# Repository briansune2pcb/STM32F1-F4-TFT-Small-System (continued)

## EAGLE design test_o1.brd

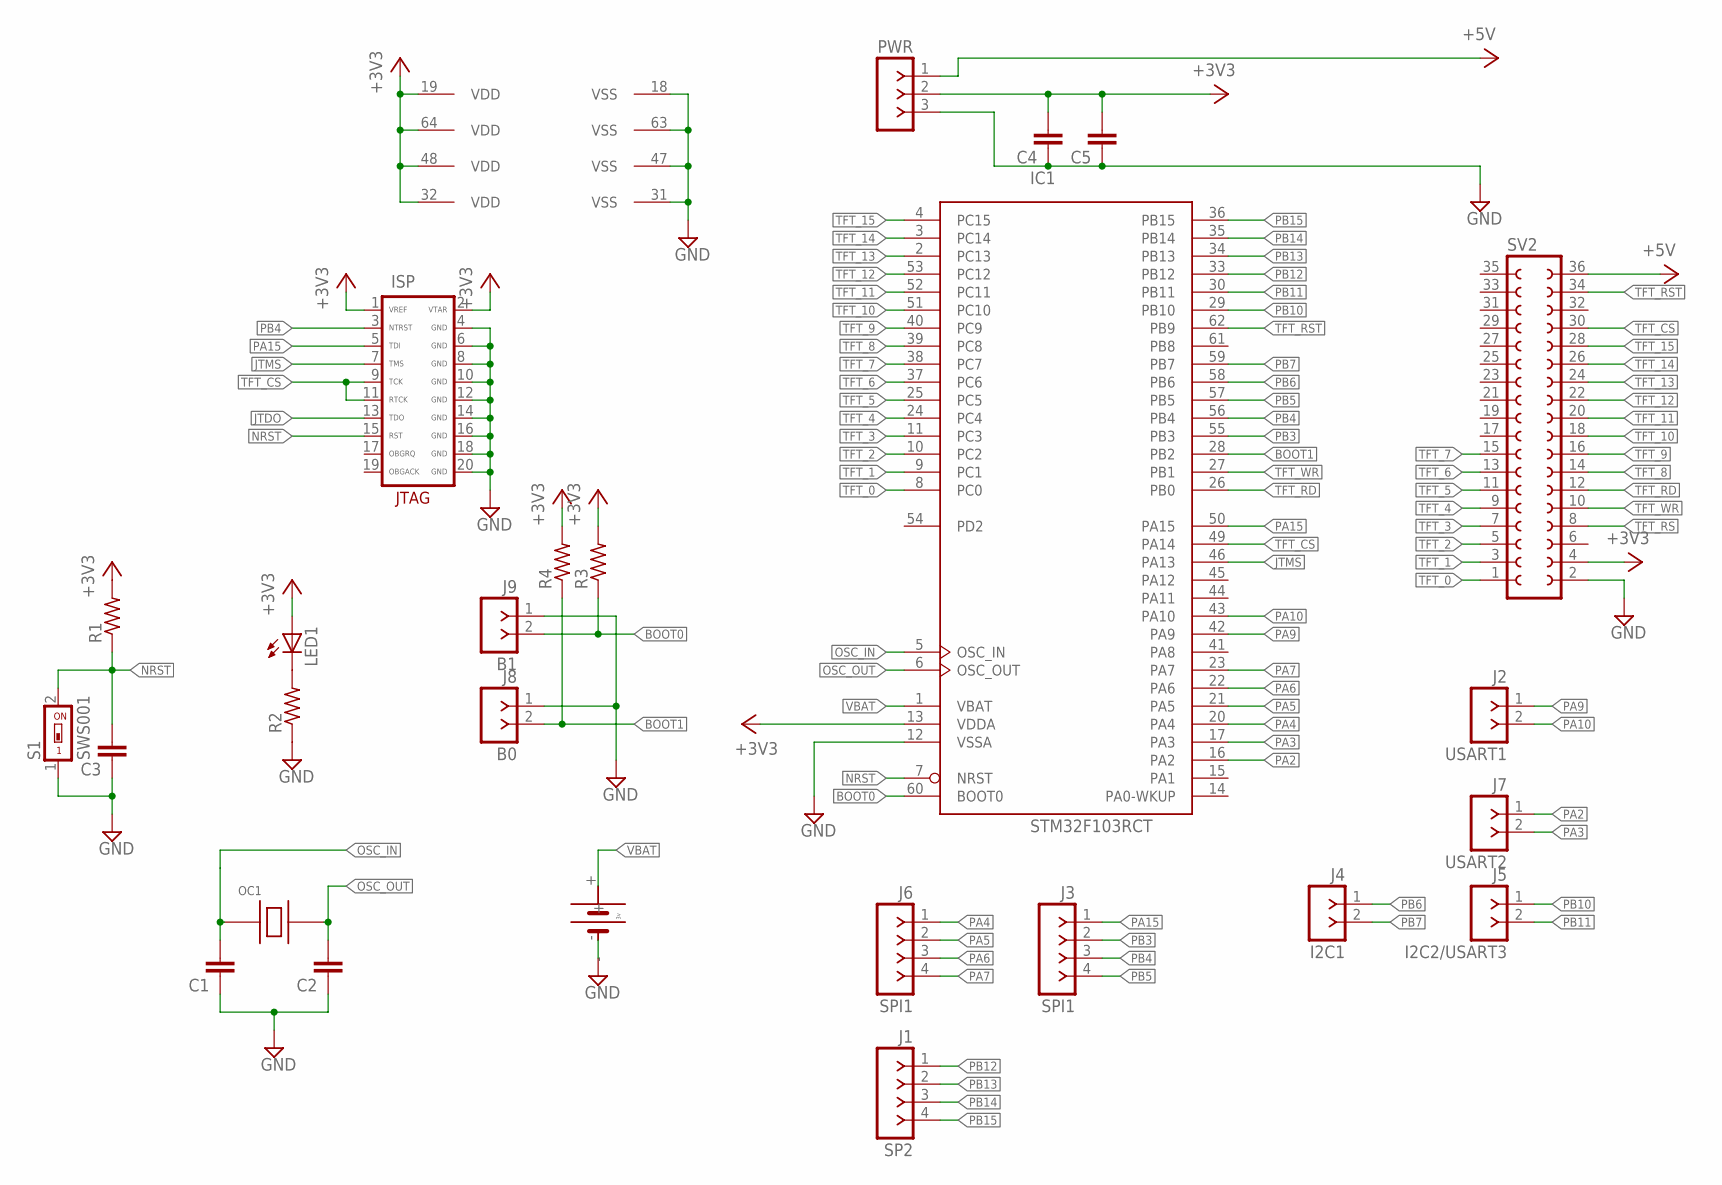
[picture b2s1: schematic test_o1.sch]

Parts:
C1, C2, C3, C4, C5: C-EUC1206; C1206
IC1: STM32F103RCT; LQFP64
ISP: JTAG; PAK100/2500-20
J1: SP2; SIP-100-04-40
J2: USART1; SIP-100-02-40
J3, J6: SPI1; SIP-100-04-40
J4: I2C1; SIP-100-02-40
J5: I2C2/USART3; SIP-100-02-40
J7: USART2; SIP-100-02-40
J8: B0; SIP-100-02-40
J9: B1; SIP-100-02-40
LED1: LEDSML1206; SML1206
OC1: SMAQ-7050B; IQG7050B
PWR: F-1X03-SIP-100-40; SIP-100-03-40
R1, R2, R3, R4: R-US_R1206; R1206
S1: SWS001; SMS-001
SV2: FE18-2
U$2: 1220BATTERY_SF; 1220BATTERY

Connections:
+3V3: C4.2, C5.2, IC1.13 (VDDA), IC1.19 (VDD), IC1.32 (VDD), IC1.48 (VDD), IC1.64 (VDD), ISP.1 (VREF), ISP.2 (VTAR), LED1.A, PWR.2, R1.2, R3.2, R4.2, SV2.4
+5V: PWR.1, SV2.36
BOOT0: IC1.60 (BOOT0), J9.2, R3.1
BOOT1: IC1.28 (PB2), J8.2, R4.1
GND: C1.1, C2.1, C3.1, C4.1, C5.1, IC1.12 (VSSA), IC1.18 (VSS), IC1.31 (VSS), IC1.47 (VSS), IC1.63 (VSS), ISP.4 (GND), ISP.6 (GND), ISP.8 (GND), ISP.10 (GND), ISP.12 (GND), ISP.14 (GND), ISP.16 (GND), ISP.18 (GND), ISP.20 (GND), J8.1, J9.1, PWR.3, R2.1, S1.1, SV2.2, U$2.-
JTDO: ISP.13 (TDO)
JTMS: IC1.46 (PA13), ISP.7 (TMS)
unnamed: LED1.C, R2.2
NRST: C3.2, IC1.7 (NRST), ISP.15 (RST), R1.1, S1.2
OSC_IN: C1.2, IC1.5 (OSC_IN), OC1.P$1 (PIN1)
OSC_OUT: C2.2, IC1.6 (OSC_OUT), OC1.P$3 (PIN2)
PA2: IC1.16 (PA2), J7.1
PA3: IC1.17 (PA3), J7.2
PA4: IC1.20 (PA4), J6.1
PA5: IC1.21 (PA5), J6.2
PA6: IC1.22 (PA6), J6.3
PA7: IC1.23 (PA7), J6.4
PA9: IC1.42 (PA9), J2.1
PA10: IC1.43 (PA10), J2.2
PA15: IC1.50 (PA15), ISP.5 (TDI), J3.1
PB3: IC1.55 (PB3), J3.2
PB4: IC1.56 (PB4), ISP.3 (NTRST), J3.3
PB5: IC1.57 (PB5), J3.4
PB6: IC1.58 (PB6), J4.1
PB7: IC1.59 (PB7), J4.2
PB10: IC1.29 (PB10), J5.1
PB11: IC1.30 (PB11), J5.2
PB12: IC1.33 (PB12), J1.1
PB13: IC1.34 (PB13), J1.2
PB14: IC1.35 (PB14), J1.3
PB15: IC1.36 (PB15), J1.4
TFT_0: IC1.8 (PC0), SV2.1
TFT_1: IC1.9 (PC1), SV2.3
TFT_2: IC1.10 (PC2), SV2.5
TFT_3: IC1.11 (PC3), SV2.7
TFT_4: IC1.24 (PC4), SV2.9
TFT_5: IC1.25 (PC5), SV2.11
TFT_6: IC1.37 (PC6), SV2.13
TFT_7: IC1.38 (PC7), SV2.15
TFT_8: IC1.39 (PC8), SV2.14
TFT_9: IC1.40 (PC9), SV2.16
TFT_10: IC1.51 (PC10), SV2.18
TFT_11: IC1.52 (PC11), SV2.20
TFT_12: IC1.53 (PC12), SV2.22
TFT_13: IC1.2 (PC13), SV2.24
TFT_14: IC1.3 (PC14), SV2.26
TFT_15: IC1.4 (PC15), SV2.28
TFT_CS: IC1.49 (PA14), ISP.9 (TCK), ISP.11 (RTCK), SV2.30
TFT_RD: IC1.26 (PB0), SV2.12
TFT_RS: SV2.8
TFT_RST: IC1.62 (PB9), SV2.34
TFT_WR: IC1.27 (PB1), SV2.10
VBAT: IC1.1 (VBAT), U$2.+

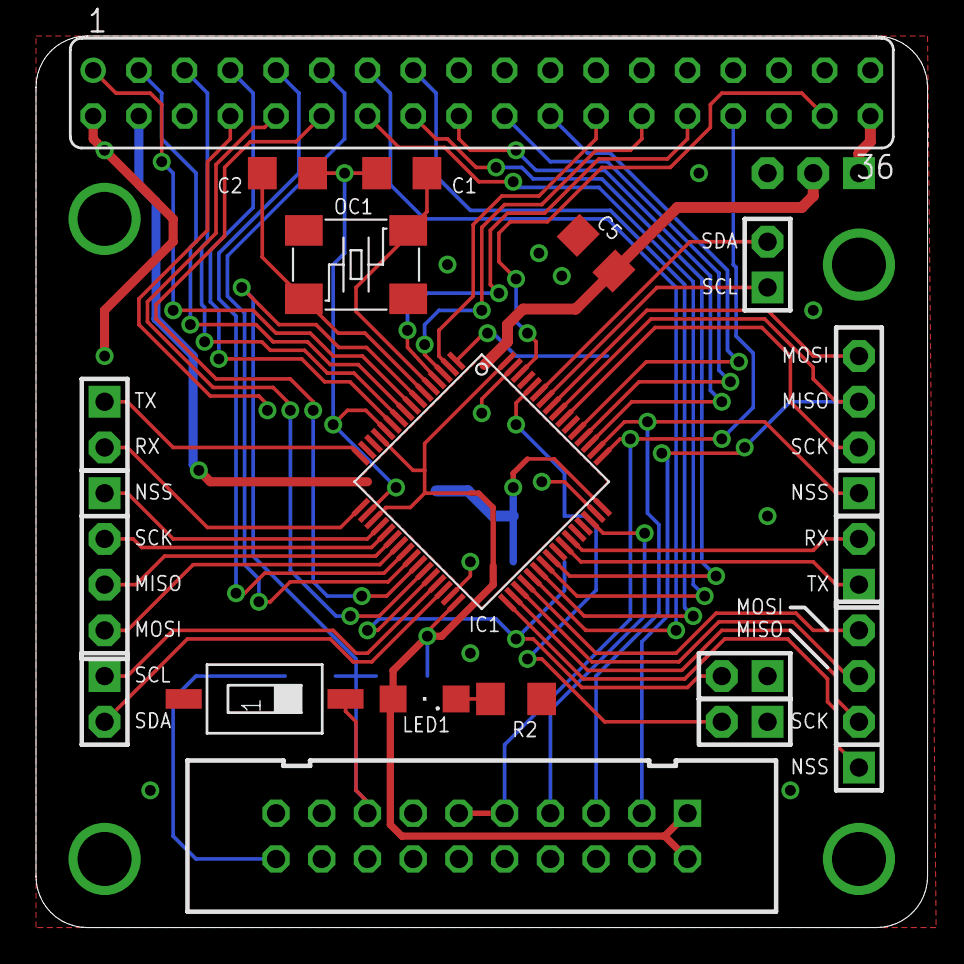
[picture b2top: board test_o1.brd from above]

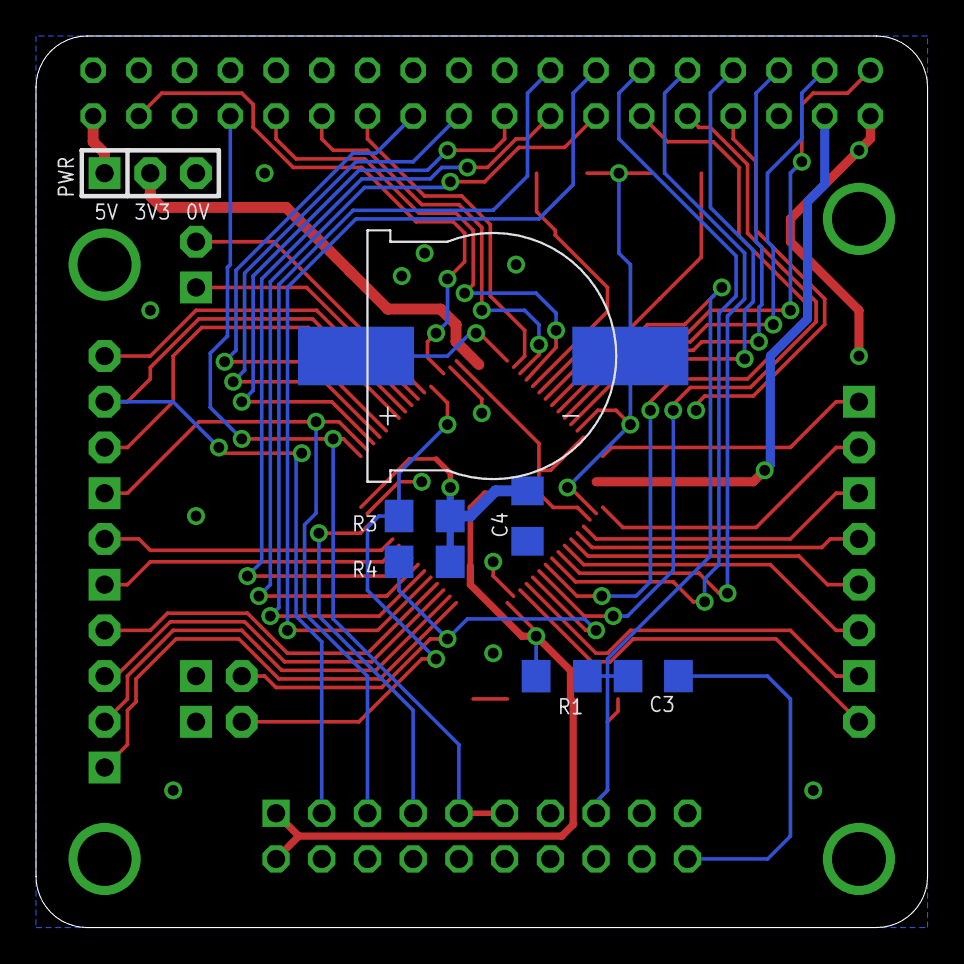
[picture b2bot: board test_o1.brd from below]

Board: 2 copper layers, 49.5 x 49.5 mm, 26 parts (7 on the bottom side), 51 nets.

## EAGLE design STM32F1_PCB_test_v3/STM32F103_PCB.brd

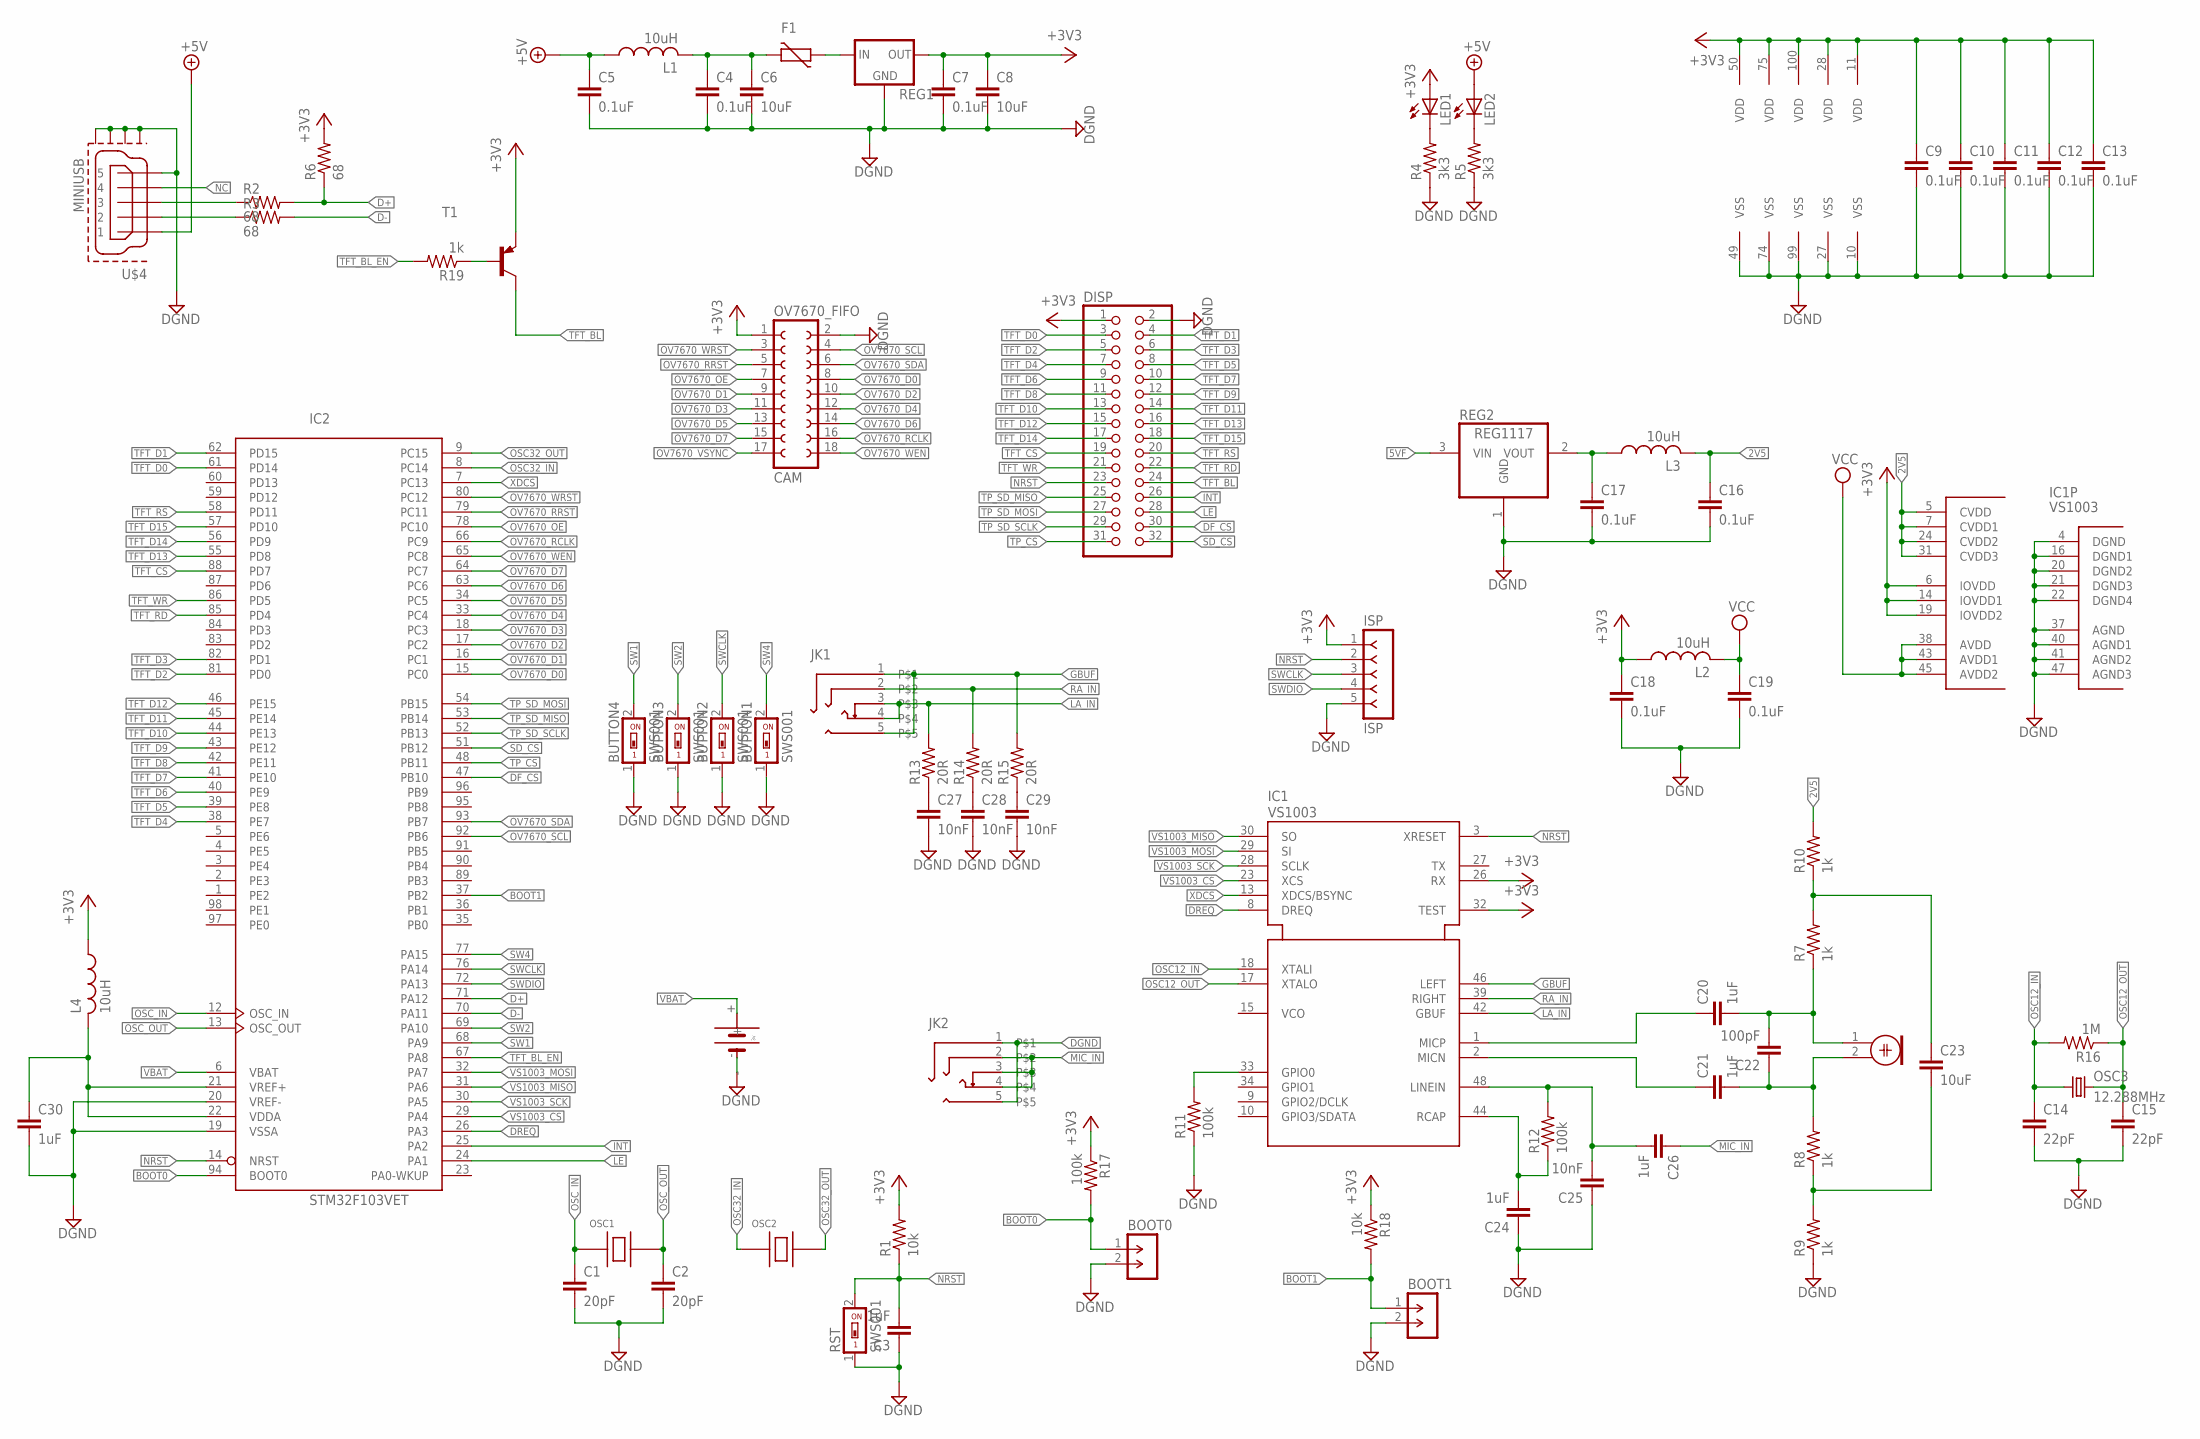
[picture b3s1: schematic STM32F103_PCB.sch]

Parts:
BOOT0, BOOT1: M-1X02-SIP-100-32; SIP-100-02-32
BUTTON1, BUTTON2, BUTTON3, BUTTON4: SWS001; SMS-001
C1, C2: 20pF; C1206
C3, C20, C21, C24, C26, C30: 1uF; C1206
C4, C5, C7, C9, C10, C11, C12, C13, C16, C17, C18, C19: 0.1uF; C1206
C6, C8, C23: 10uF; C1206
C14, C15: 22pF; C1206
C22: 100pF; C1206
C25, C27, C28, C29: 10nF; C1206
CAM: OV7670_FIFO; FE09-2
DISP: PINHD-2X16; 2X16
F1: VARISTORCN1206; CT/CN1206
IC1: VS1003; LQFP48
IC2: STM32F103VET; LQFP100
ISP: ISP; SIP-100-05-40
JK1, JK2: HEADPHONE_XXX1
L1, L2, L3, L4: 10uH; L3216C
LED1, LED2: LEDSML1206; SML1206
MIC: ELECTRET_MICROPHON-WM-61A; WM-61A
OSC1: 8.0MHz; IQG7050B
OSC2: 32.768kHz; IQG5032A
OSC3: 12.288MHz; HC49UP
R1, R18: 10k; R1206
R2, R3, R6: 68; R1206
R4, R5: 3k3; R1206
R7, R8, R9, R10, R19: 1k; R1206
R11, R12, R17: 100k; R1206
R13, R14, R15: 20R; R1206
R16: 1M; R1206
REG1: XC63FPM; SOT23
REG2: REG1117; SOT223
RST: SWS001; SMS-001
T1: MMBT3906LT1-PNP-SOT23-BEC; SOT23-BEC
U$1: 1220BATTERY_SF; 1220BATTERY
U$4: MINIUSB; MK5P

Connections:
2V5: C16.1, IC1.5 (CVDD), IC1.7 (CVDD1), IC1.24 (CVDD2), IC1.31 (CVDD3), L3.2, R10.2
5VF: F1.1, REG1.3 (IN), REG2.3 (VIN)
+3V3: C7.1, C8.1, C9.1, C10.1, C11.1, C12.1, C13.1, C18.1, CAM.1, DISP.1, IC1.6 (IOVDD), IC1.14 (IOVDD1), IC1.19 (IOVDD2), IC1.26 (RX), IC1.32 (TEST), IC2.11 (VDD), IC2.28 (VDD), IC2.50 (VDD), IC2.75 (VDD), IC2.100 (VDD), ISP.1, L2.1, L4.1, LED1.A, R1.2, R6.2, R17.1, R18.1, REG1.2 (OUT), T1.E
+5V: C5.1, L1.1, LED2.A, U$4.1
BOOT0: BOOT0.1, IC2.94 (BOOT0), R17.2
BOOT1: BOOT1.1, IC2.37 (PB2), R18.2
D+: IC2.71 (PA12), R2.2, R6.1
D-: IC2.70 (PA11), R3.2
DF_CS: DISP.30, IC2.47 (PB10)
DGND: BOOT0.2, BOOT1.2, BUTTON1.1, BUTTON2.1, BUTTON3.1, BUTTON4.1, C1.2, C2.2, C3.1, C4.2, C5.2, C6.2, C7.2, C8.2, C9.2, C10.2, C11.2, C12.2, C13.2, C14.2, C15.2, C16.2, C17.2, C18.2, C19.2, C24.1, C25.1, C27.2, C28.2, C29.2, C30.2, CAM.2, DISP.2, IC1.4 (DGND), IC1.16 (DGND1), IC1.20 (DGND2), IC1.21 (DGND3), IC1.22 (DGND4), IC1.37 (AGND), IC1.40 (AGND1), IC1.41 (AGND2), IC1.47 (AGND3), IC2.10 (VSS), IC2.19 (VSSA), IC2.20 (VREF-), IC2.27 (VSS), IC2.49 (VSS), IC2.74 (VSS), IC2.99 (VSS), ISP.5, JK2.1, JK2.5, R4.1, R5.1, R9.1, R11.1, REG1.1 (GND), REG2.1 (GND), RST.1, U$1.-, U$4.5, U$4.P$1 (GND1), U$4.P$2 (GND2), U$4.P$6 (GND3), U$4.P$7 (GND4)
DREQ: IC1.8 (DREQ), IC2.26 (PA3)
GBUF: IC1.46 (LEFT), JK1.1, JK1.5, R15.2
INT: DISP.26, IC2.25 (PA2)
LA_IN: IC1.42 (GBUF), JK1.3, JK1.4, R13.2
LE: DISP.28, IC2.24 (PA1)
MIC_IN: C26.1, JK2.2, JK2.3, JK2.4
unnamed: C17.1, L3.1, REG2.2 (VOUT)
unnamed: R3.1, U$4.2
unnamed: R2.1, U$4.3
unnamed: C4.1, C6.1, F1.2, L1.2
unnamed: LED1.C, R4.2
unnamed: LED2.C, R5.2
unnamed: C20.1, IC1.1 (MICP)
unnamed: C21.1, IC1.2 (MICN)
unnamed: C21.2, C22.1, MIC.2, R8.2
unnamed: C20.2, C22.2, MIC.1, R7.1
unnamed: C23.1, R7.2, R10.1
unnamed: C23.2, R8.1, R9.2
unnamed: IC1.33 (GPIO0), R11.2
unnamed: C24.2, IC1.44 (RCAP), R12.1
unnamed: C25.2, C26.2, IC1.48 (LINEIN), R12.2
unnamed: C27.1, R13.1
unnamed: R19.1, T1.B
unnamed: C28.1, R14.1
unnamed: C29.1, R15.1
unnamed: C30.1, IC2.21 (VREF+), IC2.22 (VDDA), L4.2
NC: U$4.4
NRST: C3.2, DISP.23, IC1.3 (XRESET), IC2.14 (NRST), ISP.2, R1.1, RST.2
OSC12_IN: C14.1, IC1.18 (XTALI), OSC3.1, R16.2
OSC12_OUT: C15.1, IC1.17 (XTALO), OSC3.2, R16.1
OSC32_IN: IC2.8 (PC14), OSC2.P$1 (PIN1)
OSC32_OUT: IC2.9 (PC15), OSC2.P$2 (PIN2)
OSC_IN: C1.1, IC2.12 (OSC_IN), OSC1.P$1 (PIN1)
OSC_OUT: C2.1, IC2.13 (OSC_OUT), OSC1.P$3 (PIN2)
OV7670_D0: CAM.8, IC2.15 (PC0)
OV7670_D1: CAM.9, IC2.16 (PC1)
OV7670_D2: CAM.10, IC2.17 (PC2)
OV7670_D3: CAM.11, IC2.18 (PC3)
OV7670_D4: CAM.12, IC2.33 (PC4)
OV7670_D5: CAM.13, IC2.34 (PC5)
OV7670_D6: CAM.14, IC2.63 (PC6)
OV7670_D7: CAM.15, IC2.64 (PC7)
OV7670_OE: CAM.7, IC2.78 (PC10)
OV7670_RCLK: CAM.16, IC2.66 (PC9)
OV7670_RRST: CAM.5, IC2.79 (PC11)
OV7670_SCL: CAM.4, IC2.92 (PB6)
OV7670_SDA: CAM.6, IC2.93 (PB7)
OV7670_VSYNC: CAM.17
OV7670_WEN: CAM.18, IC2.65 (PC8)
OV7670_WRST: CAM.3, IC2.80 (PC12)
RA_IN: IC1.39 (RIGHT), JK1.2, R14.2
SD_CS: DISP.32, IC2.51 (PB12)
SW1: BUTTON4.2, IC2.68 (PA9)
SW2: BUTTON3.2, IC2.69 (PA10)
SW4: BUTTON1.2, IC2.77 (PA15)
SWCLK: BUTTON2.2, IC2.76 (PA14), ISP.3
SWDIO: IC2.72 (PA13), ISP.4
TFT_BL: DISP.24, T1.C
TFT_BL_EN: IC2.67 (PA8), R19.2
TFT_CS: DISP.19, IC2.88 (PD7)
TFT_D0: DISP.3, IC2.61 (PD14)
TFT_D1: DISP.4, IC2.62 (PD15)
TFT_D2: DISP.5, IC2.81 (PD0)
TFT_D3: DISP.6, IC2.82 (PD1)
TFT_D4: DISP.7, IC2.38 (PE7)
TFT_D5: DISP.8, IC2.39 (PE8)
TFT_D6: DISP.9, IC2.40 (PE9)
TFT_D7: DISP.10, IC2.41 (PE10)
TFT_D8: DISP.11, IC2.42 (PE11)
TFT_D9: DISP.12, IC2.43 (PE12)
TFT_D10: DISP.13, IC2.44 (PE13)
TFT_D11: DISP.14, IC2.45 (PE14)
TFT_D12: DISP.15, IC2.46 (PE15)
TFT_D13: DISP.16, IC2.55 (PD8)
TFT_D14: DISP.17, IC2.56 (PD9)
TFT_D15: DISP.18, IC2.57 (PD10)
TFT_RD: DISP.22, IC2.85 (PD4)
TFT_RS: DISP.20, IC2.58 (PD11)
TFT_WR: DISP.21, IC2.86 (PD5)
TP_CS: DISP.31, IC2.48 (PB11)
TP_SD_MISO: DISP.25, IC2.53 (PB14)
TP_SD_MOSI: DISP.27, IC2.54 (PB15)
TP_SD_SCLK: DISP.29, IC2.52 (PB13)
VBAT: IC2.6 (VBAT), U$1.+
VCC: C19.1, IC1.38 (AVDD), IC1.43 (AVDD1), IC1.45 (AVDD2), L2.2
VS1003_CS: IC1.23 (XCS), IC2.29 (PA4)
VS1003_MISO: IC1.30 (SO), IC2.31 (PA6)
VS1003_MOSI: IC1.29 (SI), IC2.32 (PA7)
VS1003_SCK: IC1.28 (SCLK), IC2.30 (PA5)
XDCS: IC1.13 (XDCS/BSYNC), IC2.7 (PC13)

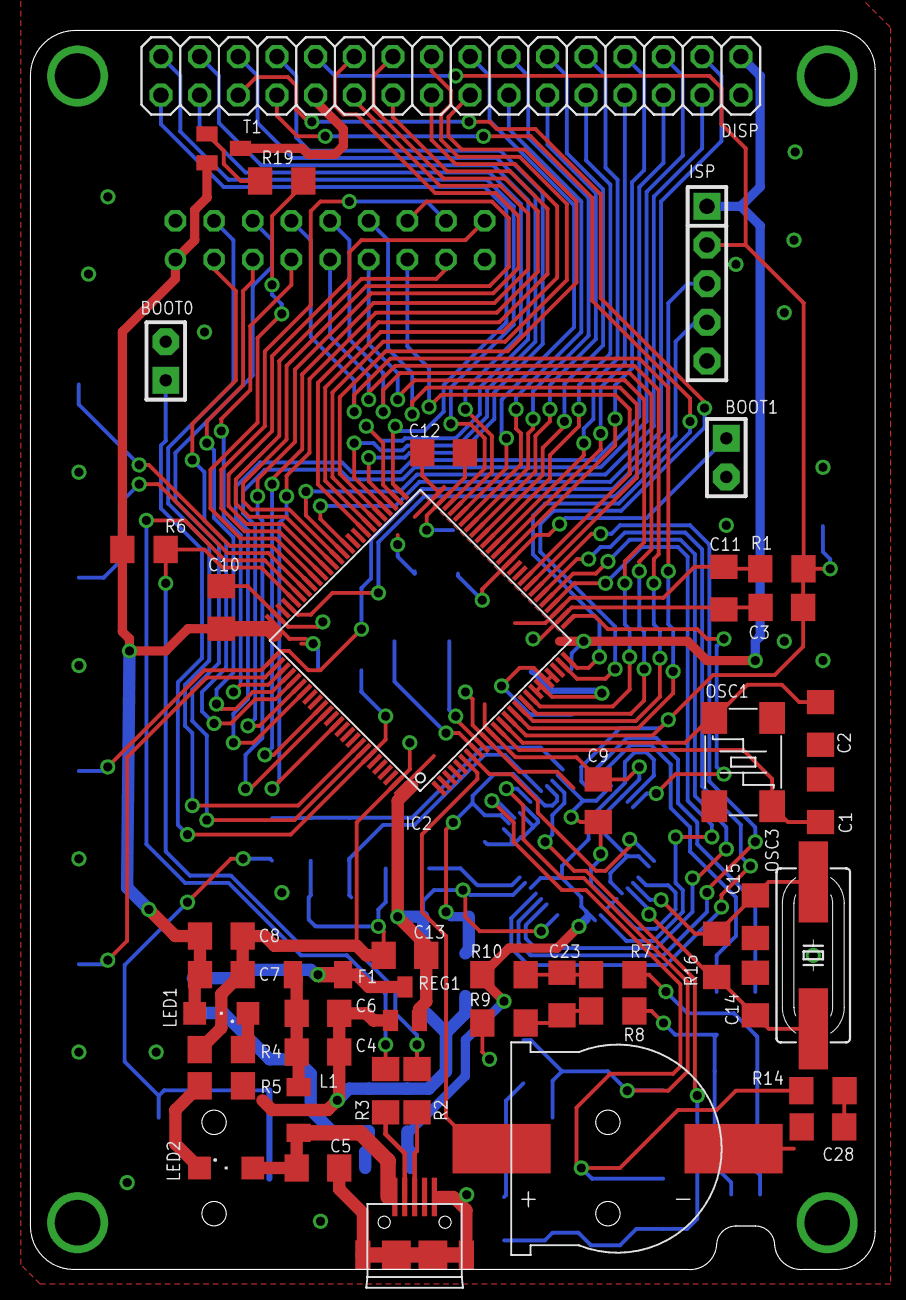
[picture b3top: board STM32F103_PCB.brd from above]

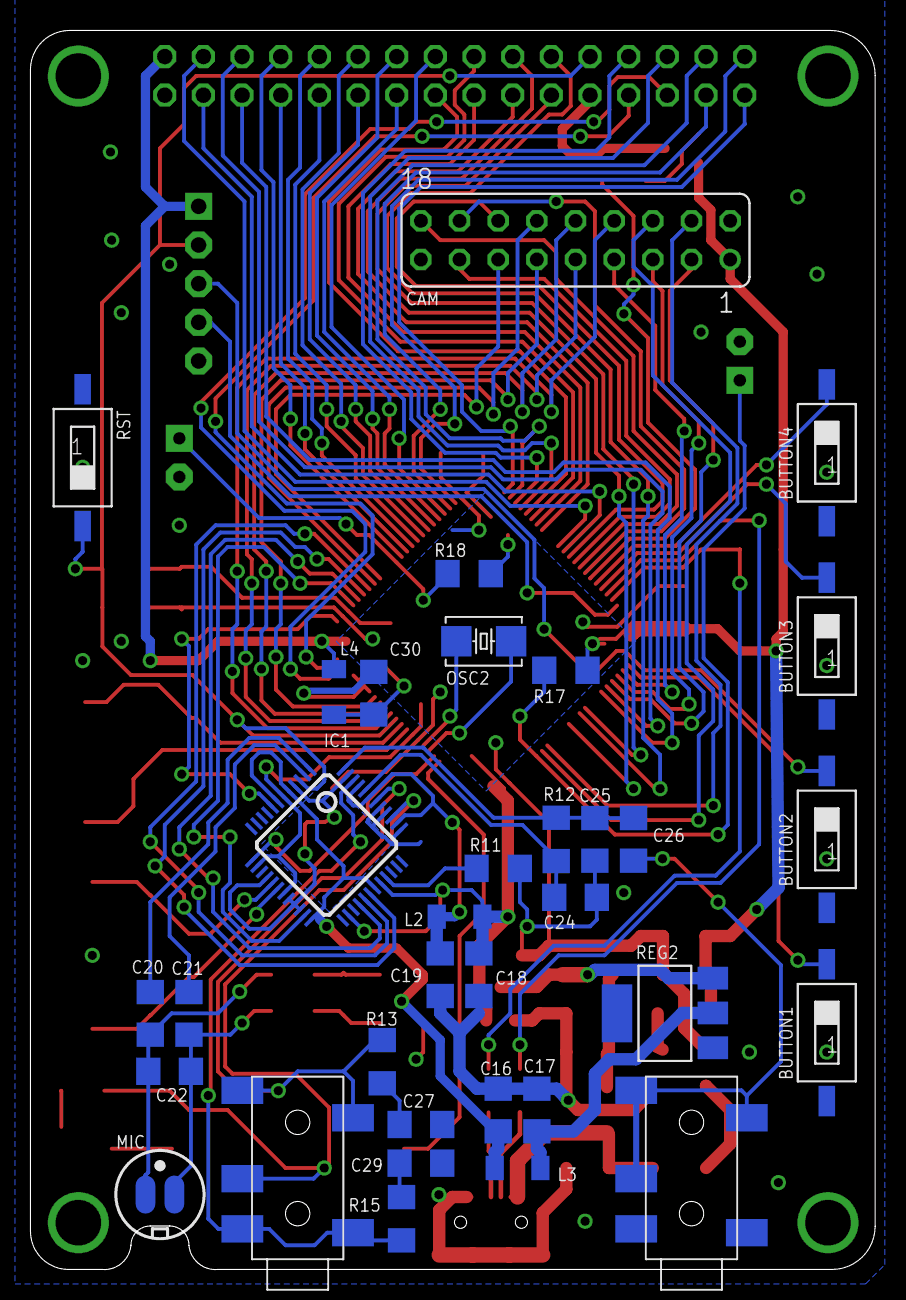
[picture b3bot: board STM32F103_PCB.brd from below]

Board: 2 copper layers, 55.5 x 81.4 mm, 79 parts (34 on the bottom side), 98 nets.

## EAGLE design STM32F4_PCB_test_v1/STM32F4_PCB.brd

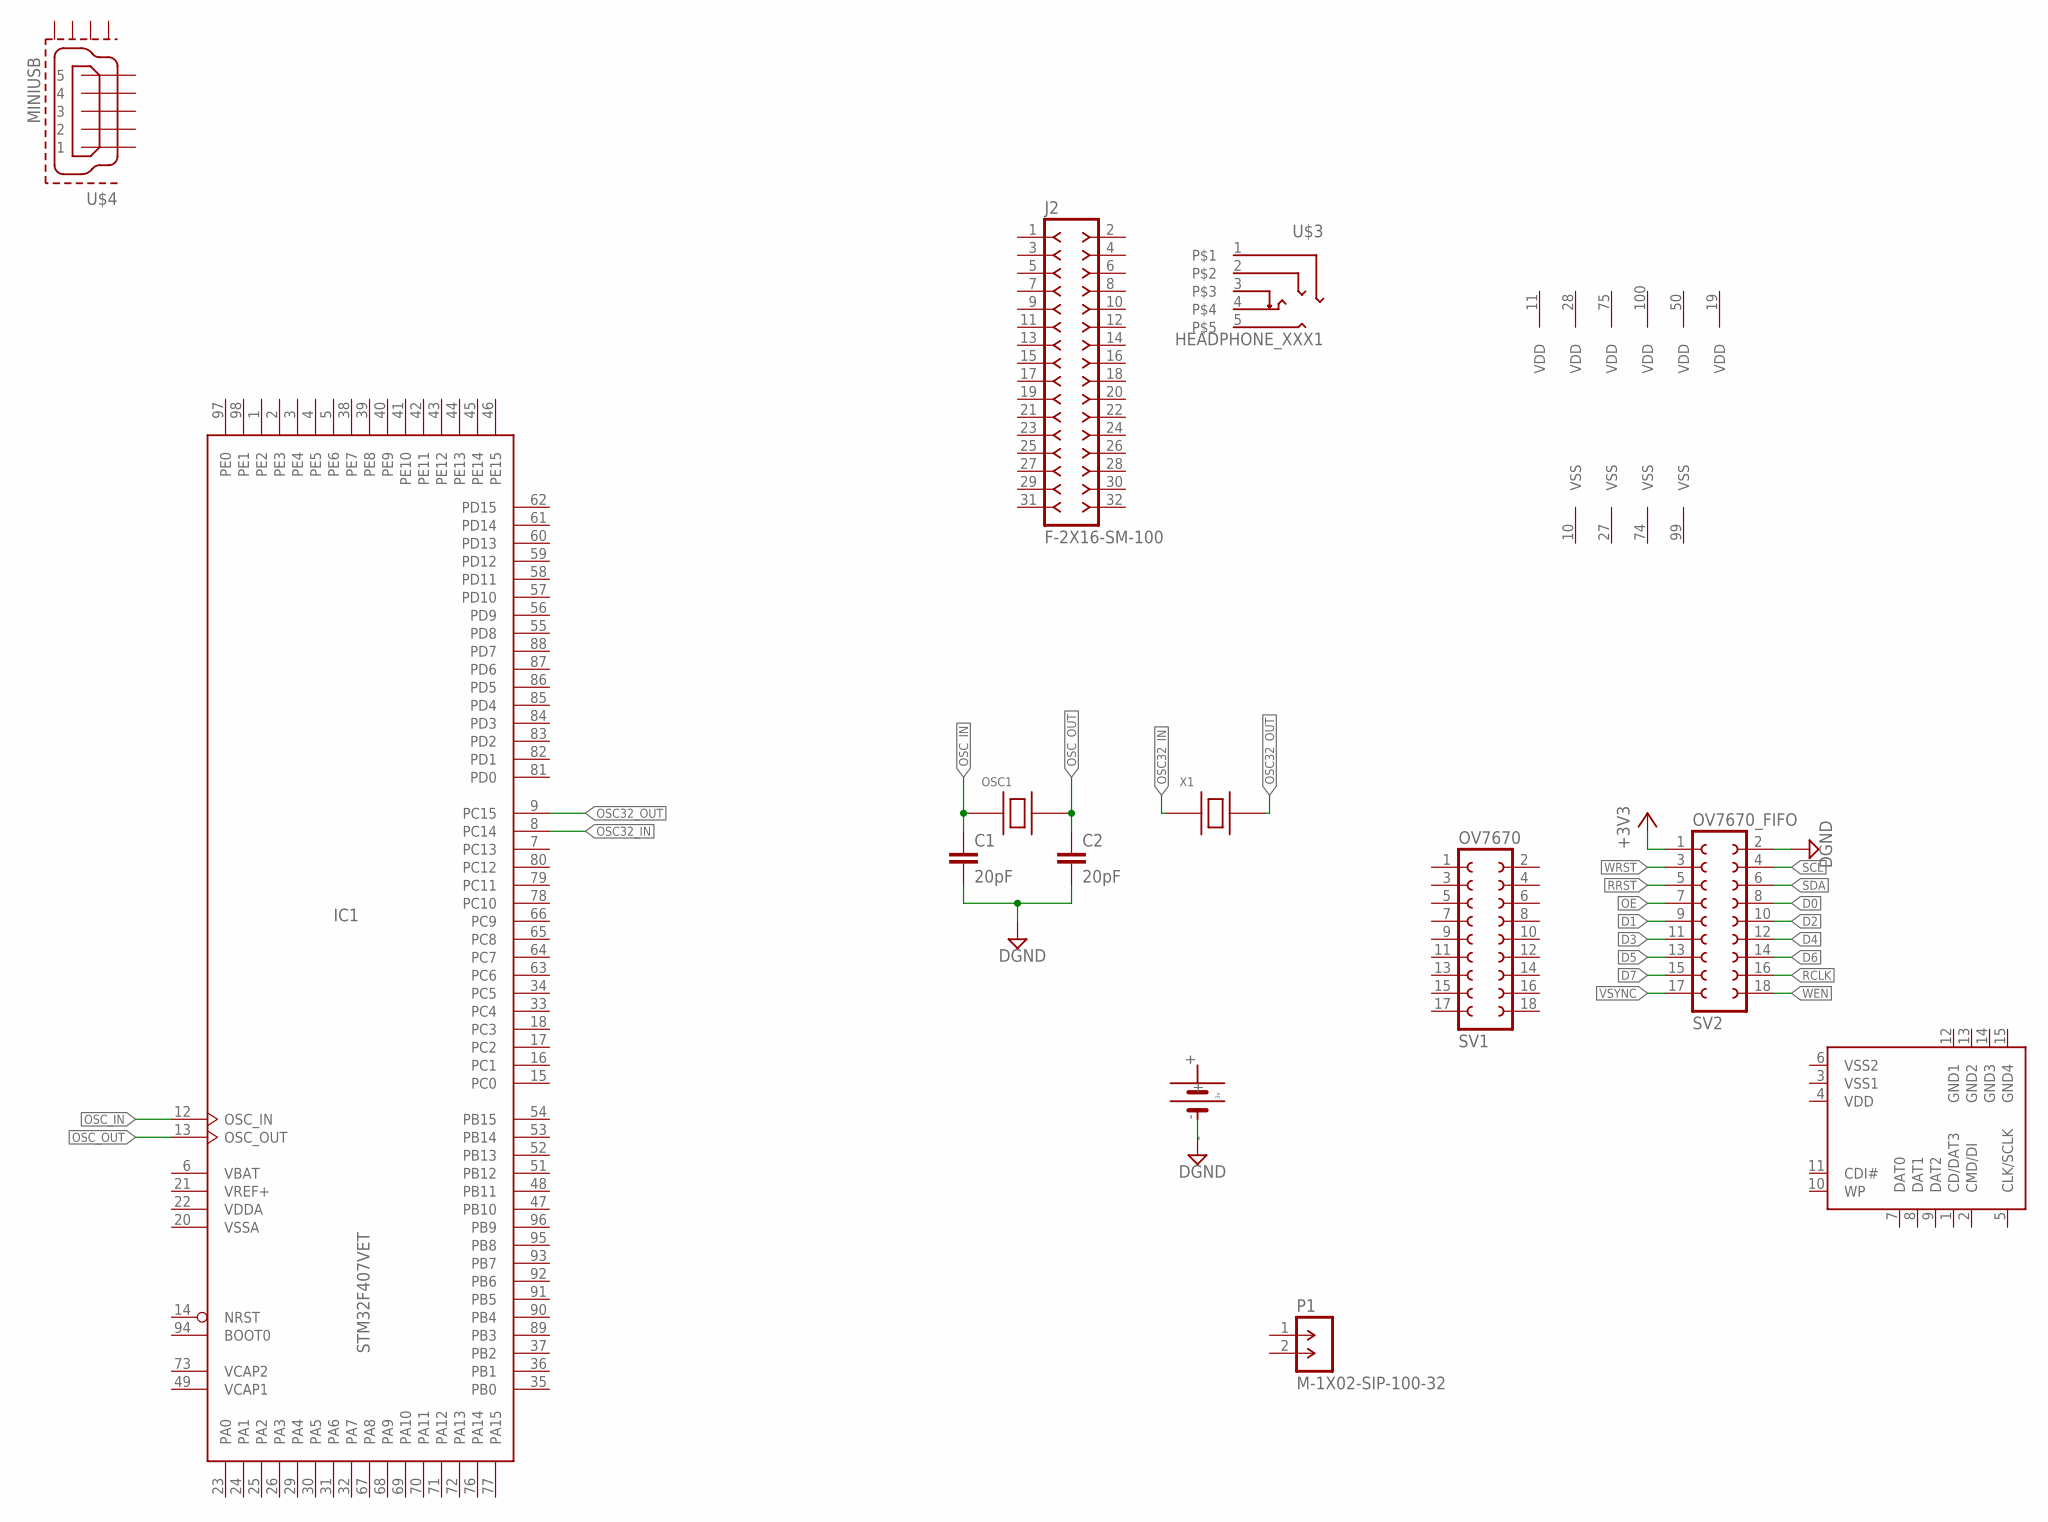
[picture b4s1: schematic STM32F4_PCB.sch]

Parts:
C1, C2: 20pF; C1206
IC1: STM32F407VET; LQFP100
J2: F-2X16-SM-100; SF-100-2X8
OSC1: 8.0MHz; IQG7050B
P1: M-1X02-SIP-100-32; SIP-100-02-32
SV1: OV7670; FE09-2W
SV2: OV7670_FIFO; FE09-2
U$1: 1220BATTERY_SF; 1220BATTERY
U$2: SDCARDVAR2; SDCMF-10915W010
U$3: HEADPHONE_XXX1
U$4: MINIUSB; MK5P
X1: 32.768kHz; IQG5032A

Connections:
+3V3: SV2.1
D0: SV2.8
D1: SV2.9
D2: SV2.10
D3: SV2.11
D4: SV2.12
D5: SV2.13
D6: SV2.14
D7: SV2.15
DGND: C1.2, C2.2, SV2.2, U$1.-
GND1: U$2.12 (GND1)
GND2: U$2.13 (GND2)
GND3: U$2.14 (GND3)
GND4: U$2.15 (GND4)
OE: SV2.7
OSC32_IN: IC1.8 (PC14), X1.P$1 (PIN1)
OSC32_OUT: IC1.9 (PC15), X1.P$2 (PIN2)
OSC_IN: C1.1, IC1.12 (OSC_IN), OSC1.P$1 (PIN1)
OSC_OUT: C2.1, IC1.13 (OSC_OUT), OSC1.P$3 (PIN2)
RCLK: SV2.16
RRST: SV2.5
SCL: SV2.4
SDA: SV2.6
VBAT: IC1.6 (VBAT)
VCAP1: IC1.49 (VCAP1)
VCAP2: IC1.73 (VCAP2)
VDD: IC1.11 (VDD), IC1.19 (VDD), IC1.28 (VDD), IC1.50 (VDD), IC1.75 (VDD), IC1.100 (VDD), U$2.4 (VDD)
VDDA: IC1.22 (VDDA)
VREF+: IC1.21 (VREF+)
VSS: IC1.10 (VSS), IC1.27 (VSS), IC1.74 (VSS), IC1.99 (VSS)
VSS1: U$2.3 (VSS1)
VSS2: U$2.6 (VSS2)
VSSA: IC1.20 (VSSA)
VSYNC: SV2.17
WEN: SV2.18
WRST: SV2.3

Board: 2 copper layers, 13 parts (2 on the bottom side), 7 nets, no tracks yet.
